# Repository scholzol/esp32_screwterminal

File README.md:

# esp32_screwterminal
This repository contains a KiCad project for a simple ESP32 DevKitC screw terminal board!

The related gerber-files are in the "gerber"- folder.

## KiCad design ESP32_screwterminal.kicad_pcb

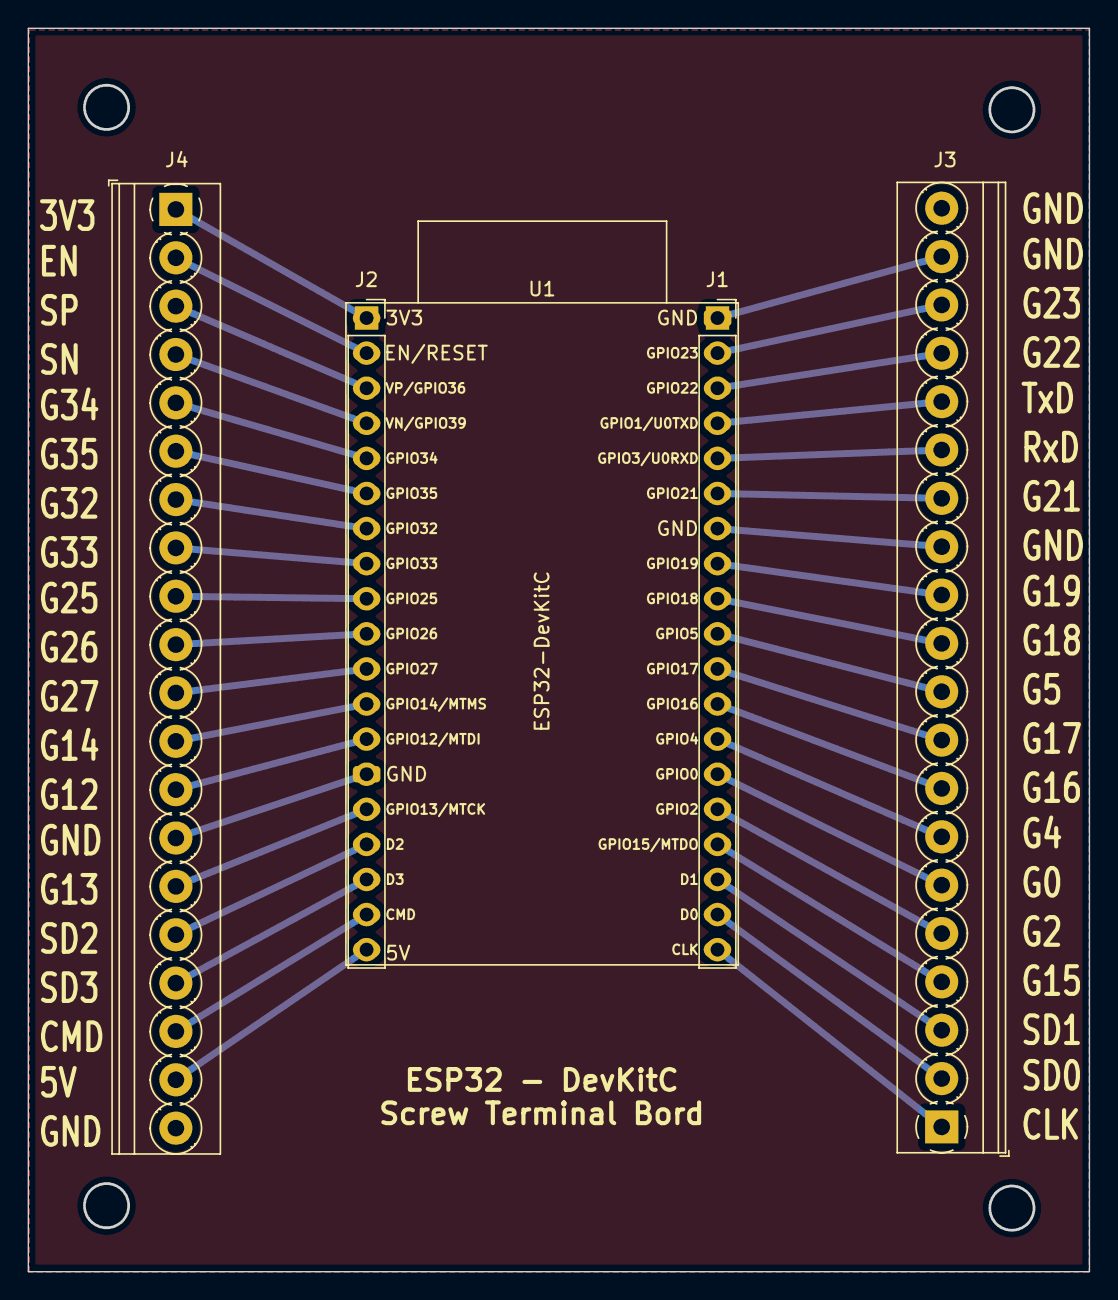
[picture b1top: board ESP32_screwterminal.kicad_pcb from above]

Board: 2 copper layers, 76.7 x 89.9 mm, 5 parts (0 on the bottom side), 38 nets.

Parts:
J1, J2: Conn_01x19_MountingPin; PinSocket_1x19_P2.54mm_Vertical
J3, J4: Screw_Terminal_01x19; TerminalBlock_Phoenix_PT-1,5-20-3.5-H_1x20_P3.50mm_Horizont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
U1: ESP32-DevKitC

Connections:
unnamed: J1.1, J3.19
unnamed: J1.2, J3.18
unnamed: J1.3, J3.17
unnamed: J1.4, J3.16
unnamed: J1.5, J3.15
unnamed: J1.6, J3.14
unnamed: J1.7, J3.13
unnamed: J1.8, J3.12
unnamed: J1.9, J3.11
unnamed: J1.10, J3.10
unnamed: J1.11, J3.9
unnamed: J1.12, J3.8
unnamed: J1.13, J3.7
unnamed: J1.14, J3.6
unnamed: J1.15, J3.5
unnamed: J1.16, J3.4
unnamed: J1.17, J3.3
unnamed: J1.18, J3.2
unnamed: J1.19, J3.1
unnamed: J2.1, J4.1
unnamed: J2.2, J4.2
unnamed: J2.3, J4.3
unnamed: J2.4, J4.4
unnamed: J2.5, J4.5
unnamed: J2.6, J4.6
unnamed: J2.7, J4.7
unnamed: J2.8, J4.8
unnamed: J2.9, J4.9
unnamed: J2.10, J4.10
unnamed: J2.11, J4.11
unnamed: J2.12, J4.12
unnamed: J2.13, J4.13
unnamed: J2.14, J4.14
unnamed: J2.15, J4.15
unnamed: J2.16, J4.16
unnamed: J2.17, J4.17
unnamed: J2.18, J4.18
unnamed: J2.19, J4.19

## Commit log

2022-05-15 First issue of esp32 devkitc screw terminal
2022-05-15 - gerber files shifted into a separate folder - some backup files deleted
2022-05-15 Create README.md
    This repository contains a KiCad project for a simple ESP32 DevKitC screw terminal block
